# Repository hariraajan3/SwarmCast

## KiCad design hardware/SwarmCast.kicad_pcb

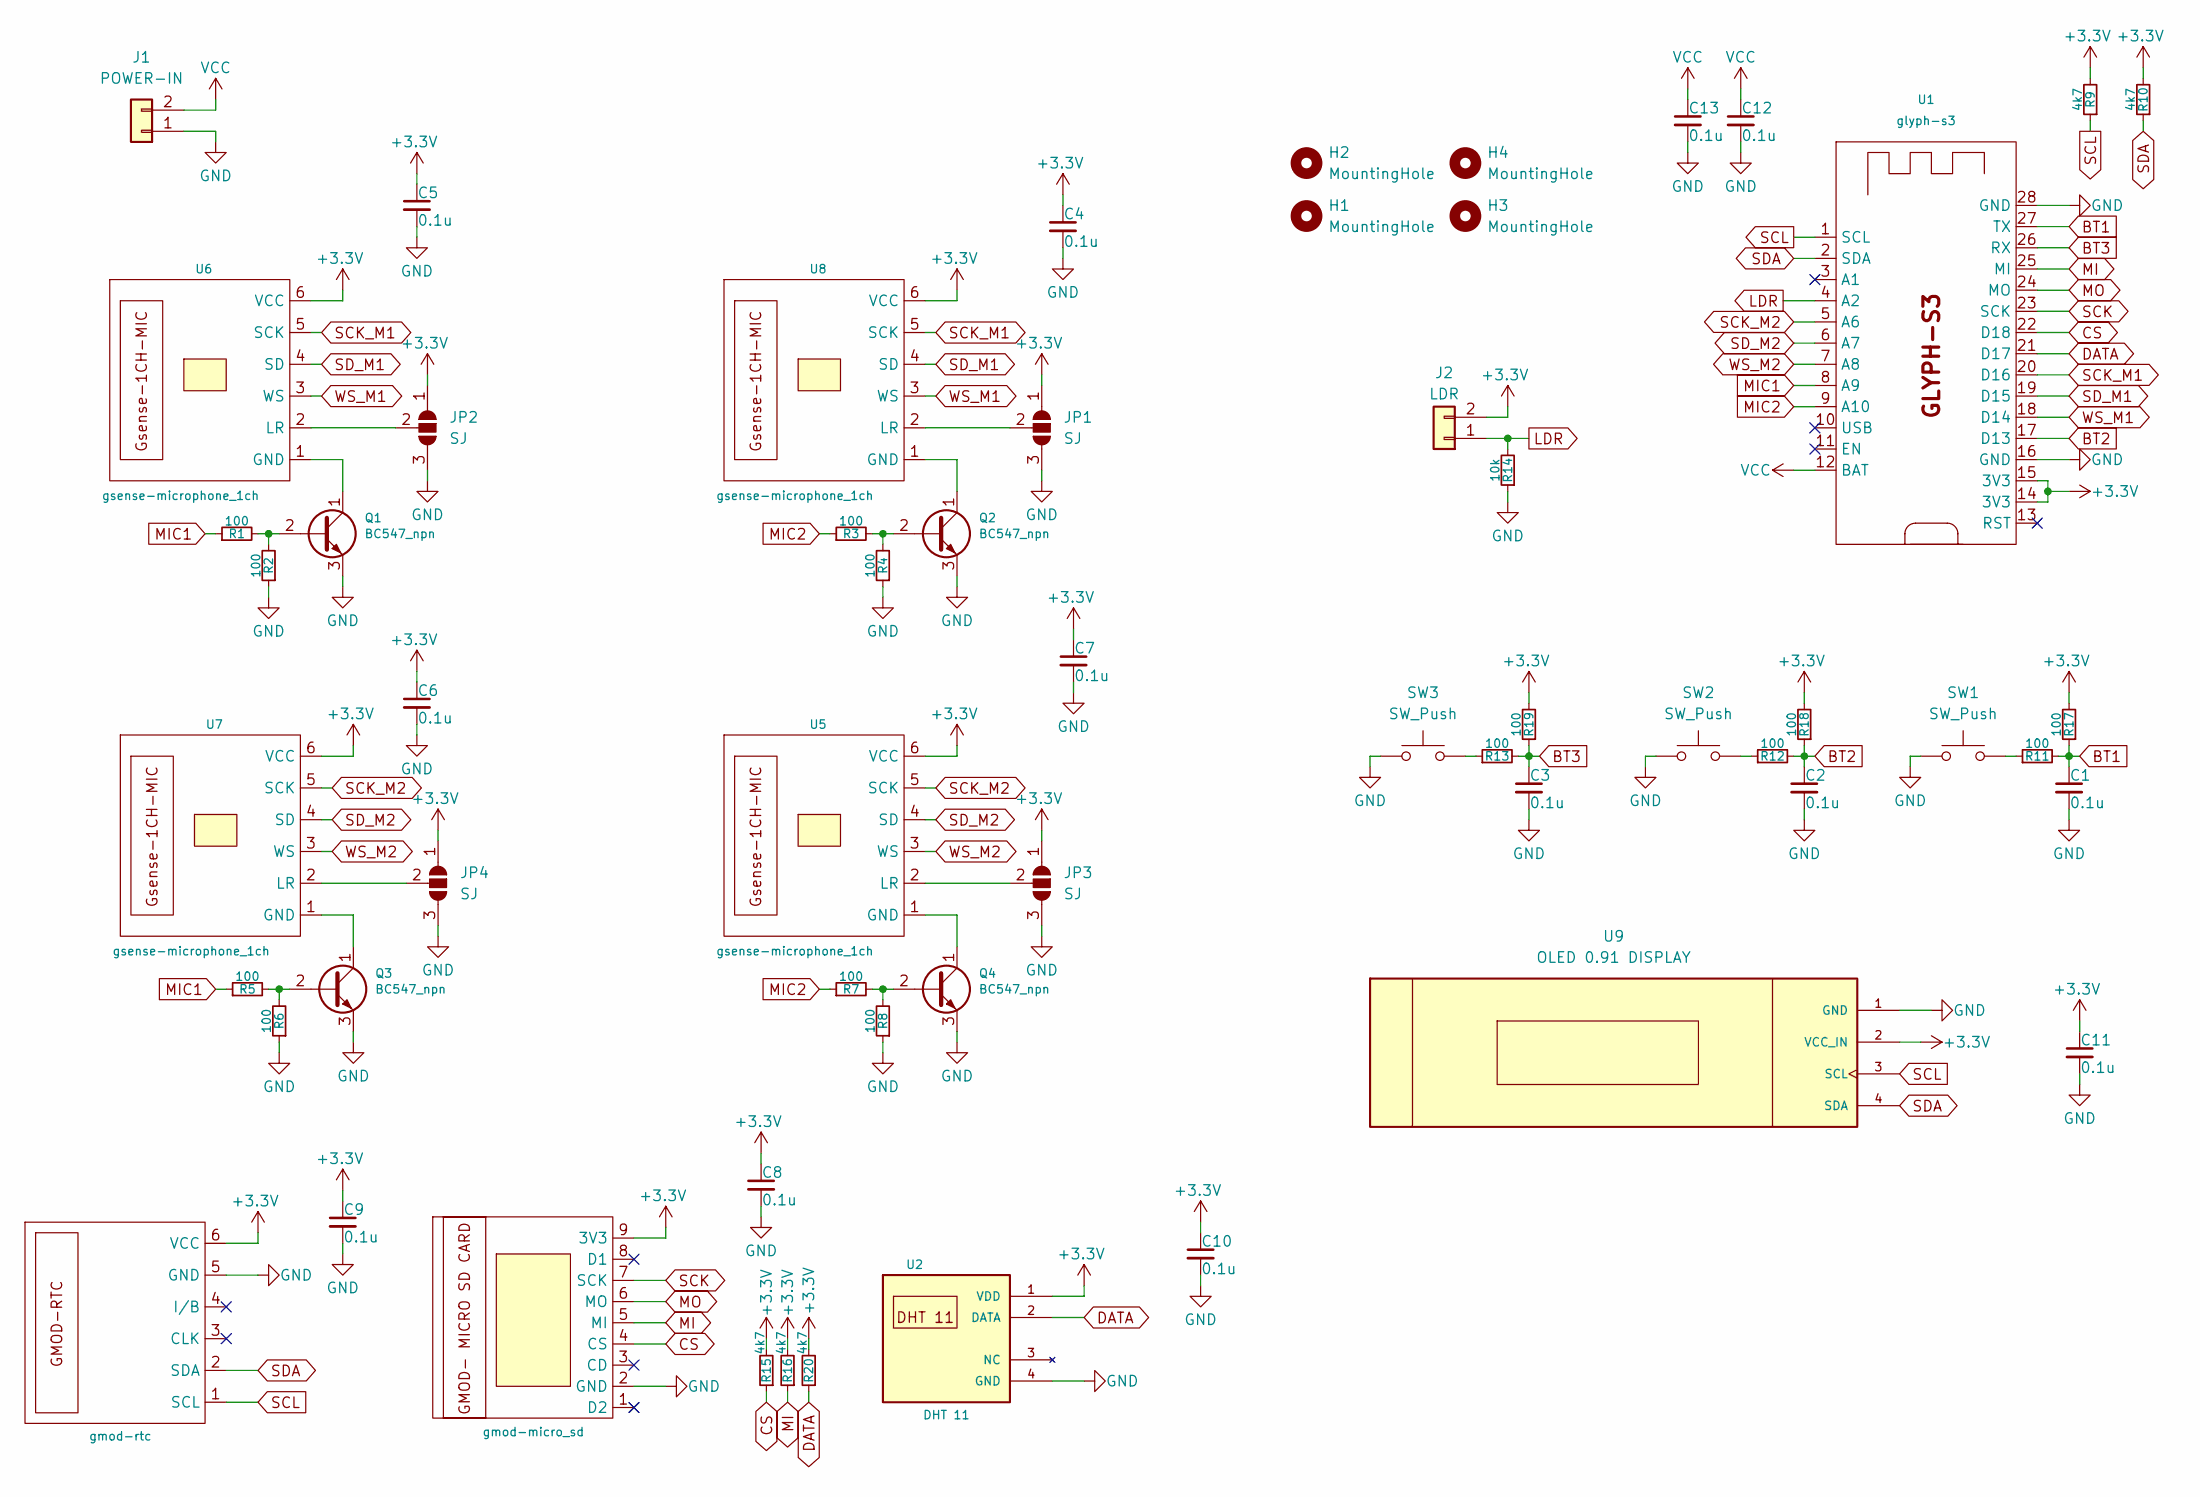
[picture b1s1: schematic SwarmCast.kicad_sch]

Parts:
C1, C2, C3, C4, C5, C6, C7, C8, C9, C10, C11, C12, C13: 0.1u; C_Disc_D5.0mm_W2.5mm_P2.50mm
H1, H2, H3, H4: MountingHole; MountingHole_3.2mm_M3
J1: POWER-IN; JST_XH_B2B-XH-A_1x02_P2.50mm_Vertical
J2: LDR; JST_XH_B2B-XH-A_1x02_P2.50mm_Vertical
JP1, JP2, JP3, JP4: SJ; SolderJumper-3_P1.3mm_Open_RoundedPad1.0x1.5mm
Q1, Q2, Q3, Q4: BC547_npn
R1, R2, R3, R4, R5, R6, R7, R8, R11, R12, R13, R17, R18, R19: 100; R_Axial_DIN0207_L6.3mm_D2.5mm_P7.62mm_Horizontal
R9, R10, R15, R16, R20: 4k7; R_Axial_DIN0207_L6.3mm_D2.5mm_P7.62mm_Horizontal
R14: 10k; R_Axial_DIN0207_L6.3mm_D2.5mm_P7.62mm_Horizontal
SW1: SW_Push; SW_PUSH-12mm
SW2, SW3: SW_Push; SW_PUSH_6mm_H5mm
U1: glyph-s3
U2: DHT 11; DHT11
U3: gmod-micro_sd
U4: gmod-rtc
U5, U6, U7, U8: gsense-microphone_1ch
U9: OLED 0.91 DISPLAY; OLED_0.91_display

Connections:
+3.3V: C4.1, C5.1, C6.1, C7.1, C8.1, C9.1, C10.1, C11.1, J2.2, JP1.1 (A), JP2.1 (A), JP3.1 (A), JP4.1 (A), R9.2, R10.2, R15.2, R16.2, R17.2, R18.2, R19.2, R20.2, U1.14 (3V3), U1.15 (3V3), U2.1 (VDD), U3.9 (3V3), U4.6 (VCC), U5.6 (VCC), U6.6 (VCC), U7.6 (VCC), U8.6 (VCC), U9.2 (VCC_IN)
BT1: C1.1, R11.2, R17.1, U1.27 (TX)
BT2: C2.1, R12.2, R18.1, U1.17 (D13)
BT3: C3.1, R13.2, R19.1, U1.26 (RX)
CS: R15.1, U1.22 (D18), U3.4 (CS)
DATA: R20.1, U1.21 (D17), U2.2 (DATA)
GND: C1.2, C2.2, C3.2, C4.2, C5.2, C6.2, C7.2, C8.2, C9.2, C10.2, C11.2, C12.2, C13.2, J1.1, JP1.3 (B), JP2.3 (B), JP3.3 (B), JP4.3 (B), Q1.3 (EMITTER), Q2.3 (EMITTER), Q3.3 (EMITTER), Q4.3 (EMITTER), R2.1, R4.1, R6.1, R8.1, R14.1, SW1.1, SW2.1, SW3.1, U1.16 (GND), U1.28 (GND), U2.4 (GND), U3.2 (GND), U4.5 (GND), U9.1 (GND)
LDR: J2.1, R14.2, U1.4 (A2)
MI: R16.1, U1.25 (MI), U3.5 (MI)
MIC1: R1.1, R5.1, U1.8 (A9)
MIC2: R3.1, R7.1, U1.9 (A10)
MO: U1.24 (MO), U3.6 (MO)
unnamed: JP1.2 (C), U8.2 (LR)
unnamed: JP2.2 (C), U6.2 (LR)
unnamed: JP3.2 (C), U5.2 (LR)
unnamed: JP4.2 (C), U7.2 (LR)
unnamed: Q1.2 (BASE), R1.2, R2.2
unnamed: Q1.1 (COLLECTOR), U6.1 (GND)
unnamed: Q2.2 (BASE), R3.2, R4.2
unnamed: Q2.1 (COLLECTOR), U8.1 (GND)
unnamed: Q3.2 (BASE), R5.2, R6.2
unnamed: Q3.1 (COLLECTOR), U7.1 (GND)
unnamed: Q4.2 (BASE), R7.2, R8.2
unnamed: Q4.1 (COLLECTOR), U5.1 (GND)
unnamed: R11.1, SW1.2
unnamed: R12.1, SW2.2
unnamed: R13.1, SW3.2
SCK: U1.23 (SCK), U3.7 (SCK)
SCK_M1: U1.20 (D16), U6.5 (SCK), U8.5 (SCK)
SCK_M2: U1.5 (A6), U5.5 (SCK), U7.5 (SCK)
SCL: R9.1, U1.1 (SCL), U4.1 (SCL), U9.3 (SCL)
SDA: R10.1, U1.2 (SDA), U4.2 (SDA), U9.4 (SDA)
SD_M1: U1.19 (D15), U6.4 (SD), U8.4 (SD)
SD_M2: U1.6 (A7), U5.4 (SD), U7.4 (SD)
VCC: C12.1, C13.1, J1.2, U1.12 (BAT)
WS_M1: U1.18 (D14), U6.3 (WS), U8.3 (WS)
WS_M2: U1.7 (A8), U5.3 (WS), U7.3 (WS)

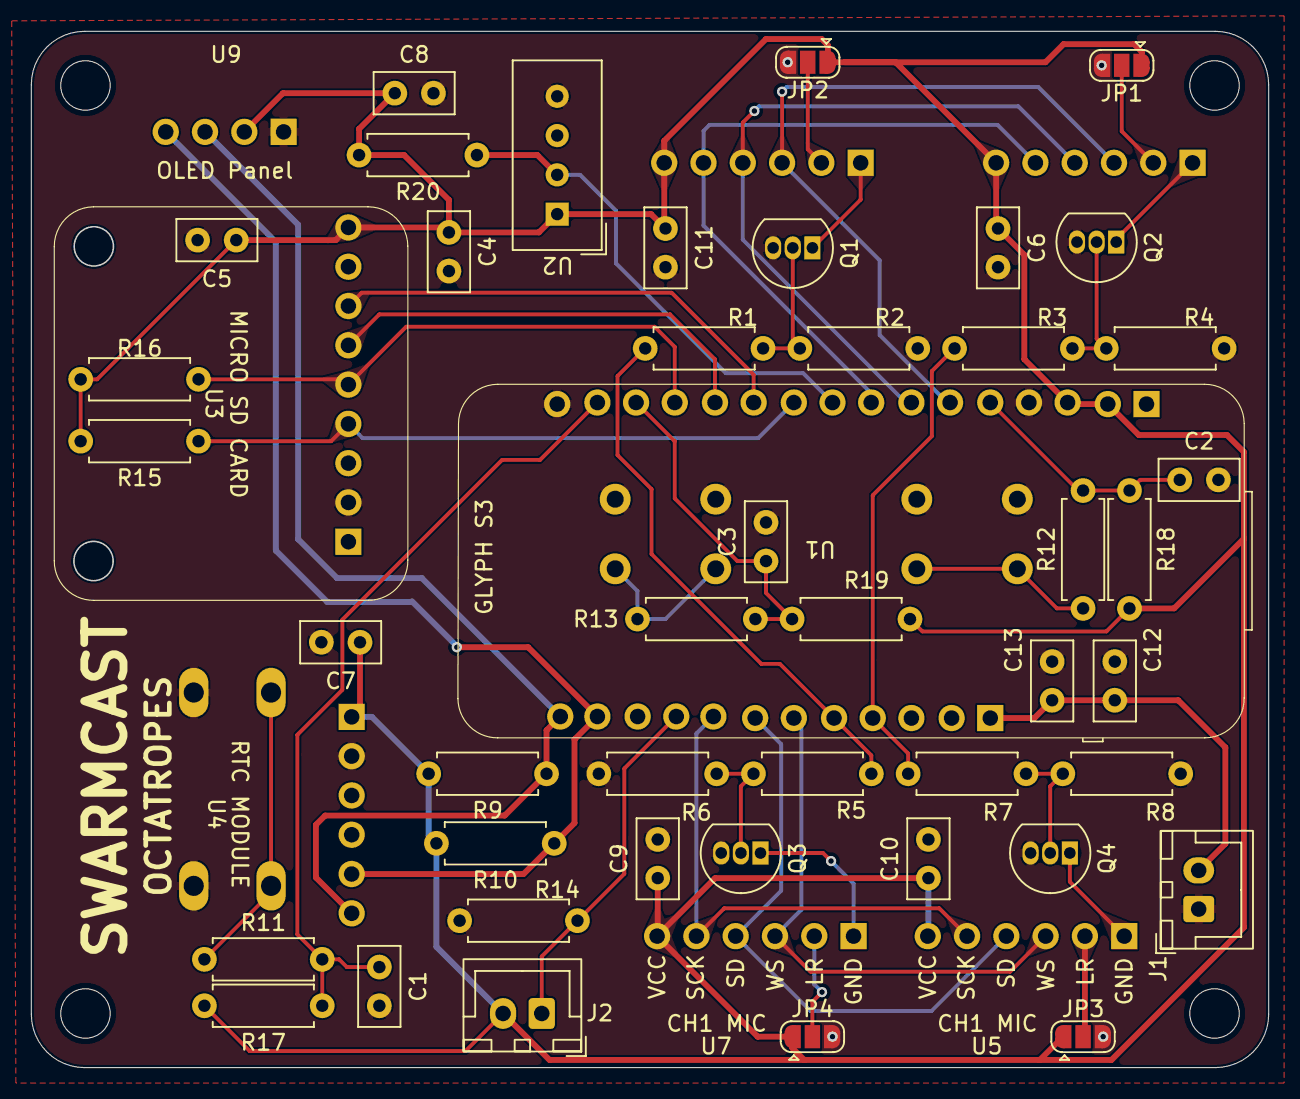
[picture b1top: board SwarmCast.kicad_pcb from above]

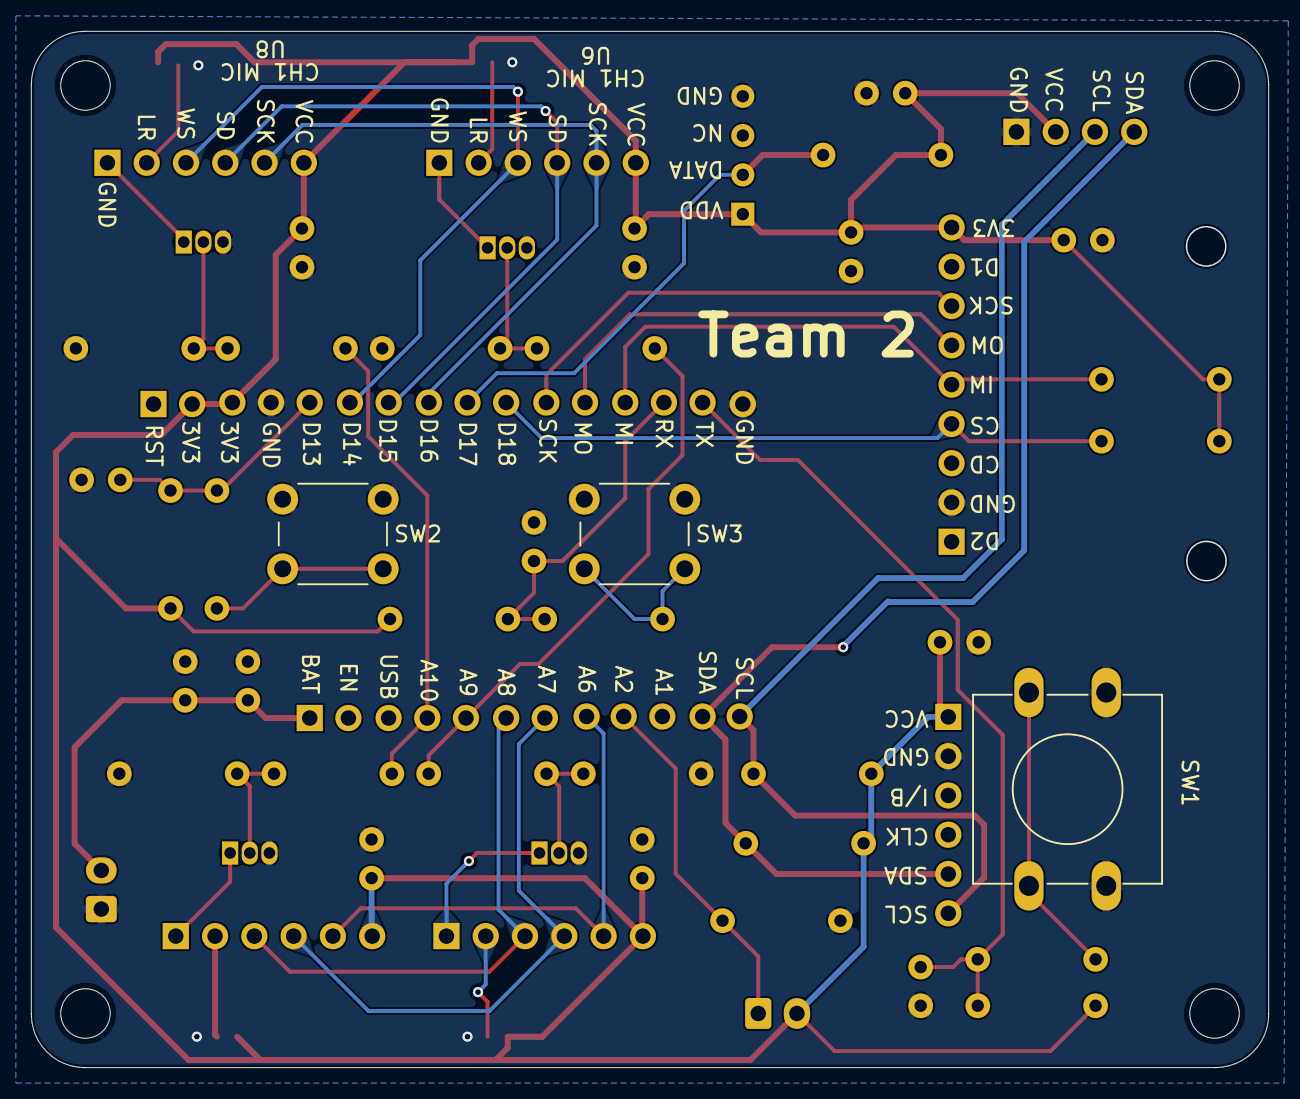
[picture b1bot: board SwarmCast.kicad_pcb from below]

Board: 2 copper layers, 80.0 x 67.0 mm, 59 parts (5 on the bottom side), 37 nets.

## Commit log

2026-04-10 initial git push
2026-04-10 hardware innit
2026-04-10 first push , Ai assistant and map UI
2026-04-11 PCB design completed
2026-04-11 updated the frontend UI part
2026-04-12 Update: PCB files
2026-04-12 updated : API calls , frontend and backend
2026-04-12 updated the rain overlay
